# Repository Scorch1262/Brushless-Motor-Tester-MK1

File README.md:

# Brushless-Motor-Tester-MK1

3D-Druck Daten:
https://makerworld.com/de/models/1416815-brushless-motor-tester-mk1

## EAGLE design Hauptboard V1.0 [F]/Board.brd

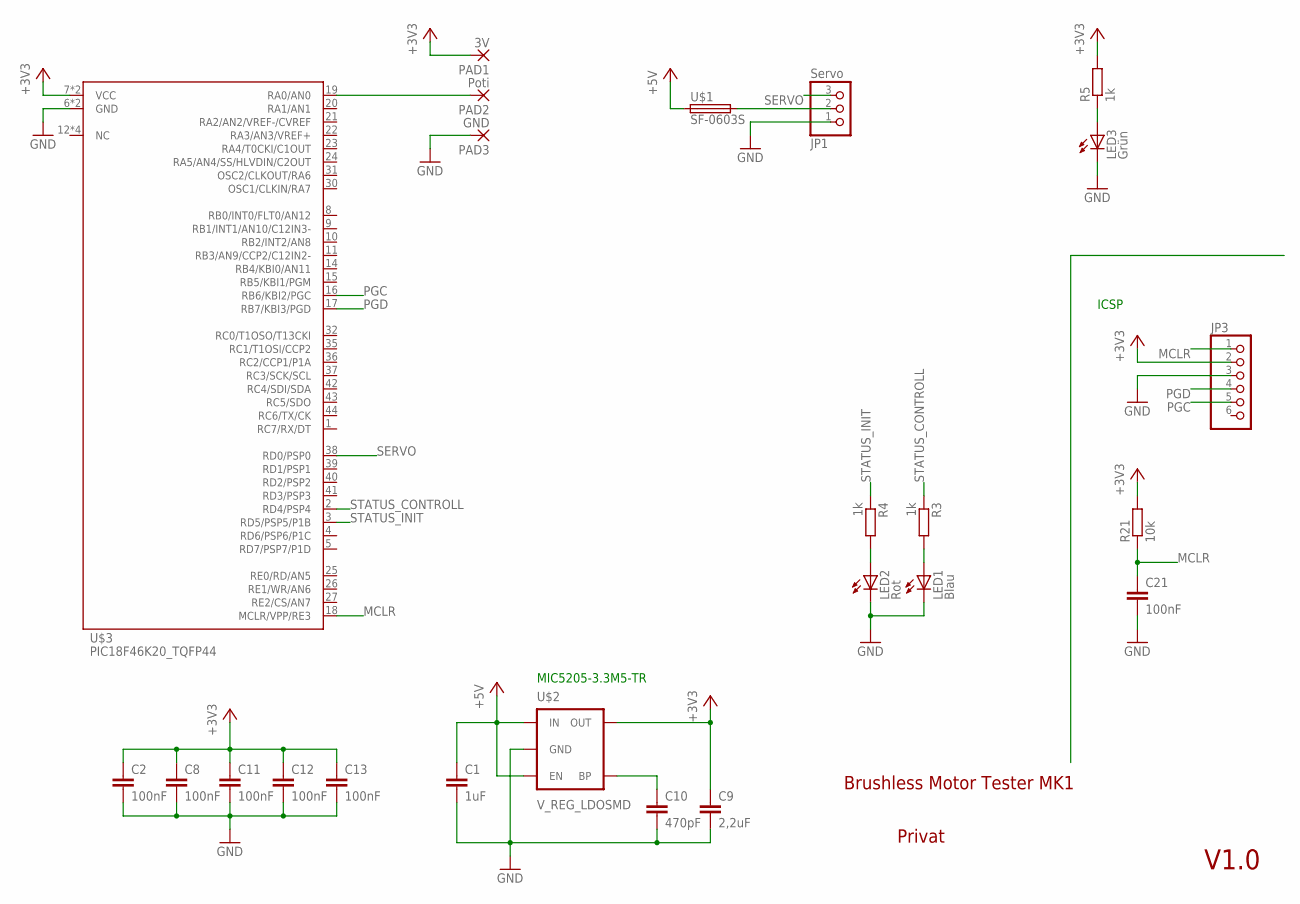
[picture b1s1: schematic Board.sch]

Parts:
C1: 1uF; C0805
C2, C8, C11, C12, C13, C21: 100nF; C0805
C9: 2,2uF; C0805
C10: 470pF; C0805
JP1: Servo; 1X03/90
JP3: PINHD-1X6; 1X06
LED1: Blau; CHIPLED_0805
LED2: Rot; CHIPLED_0805
LED3: Grün; CHIPLED_0805
PAD1: 3V; 5-1,8_50
PAD2: Poti; 5-1,8_50
PAD3: GND; 5-1,8_50
R3, R4, R5: 1k; R0805
R21: 10k; R0805
U$1: SF-0603S; R0603
U$2: V_REG_LDOSMD; SOT23-5
U$3: PIC18F46K20_TQFP44; TQFP44

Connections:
+3V3: C2.1, C8.1, C9.1, C11.1, C12.1, C13.1, JP3.2, PAD1.1, R5.2, R21.2, U$2.5 (OUT), U$3.7 (VCC), U$3.28 (VCC)
+5V: C1.1, U$1.1, U$2.1 (IN), U$2.3 (EN)
GND: C1.2, C2.2, C8.2, C9.2, C10.2, C11.2, C12.2, C13.2, C21.2, JP1.1, JP3.3, LED1.C, LED2.C, LED3.C, PAD3.1, U$2.2 (GND), U$3.6 (GND), U$3.29 (GND)
MCLR: C21.1, JP3.1, R21.1, U$3.18 (MCLR/VPP/RE3)
unnamed: PAD2.1, U$3.19 (RA0/AN0)
unnamed: JP1.2, U$1.2
unnamed: LED3.A, R5.1
unnamed: LED1.A, R3.2
unnamed: LED2.A, R4.2
unnamed: C10.1, U$2.4 (BP)
PGC: JP3.5, U$3.16 (RB6/KBI2/PGC)
PGD: JP3.4, U$3.17 (RB7/KBI3/PGD)
SERVO: JP1.3, U$3.38 (RD0/PSP0)
STATUS_CONTROLL: R3.1, U$3.2 (RD4/PSP4)
STATUS_INIT: R4.1, U$3.3 (RD5/PSP5/P1B)

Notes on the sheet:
Brushless Motor Tester MK1
Privat
V1.0
ICSP
MIC5205-3.3M5-TR

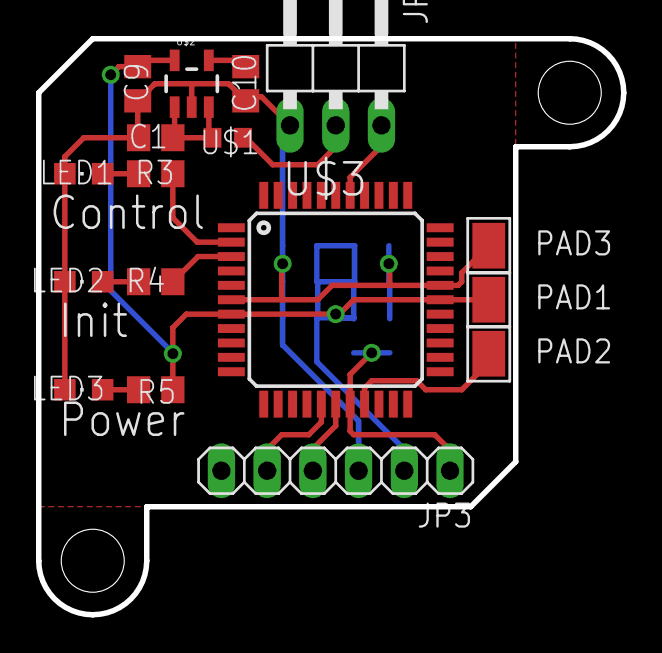
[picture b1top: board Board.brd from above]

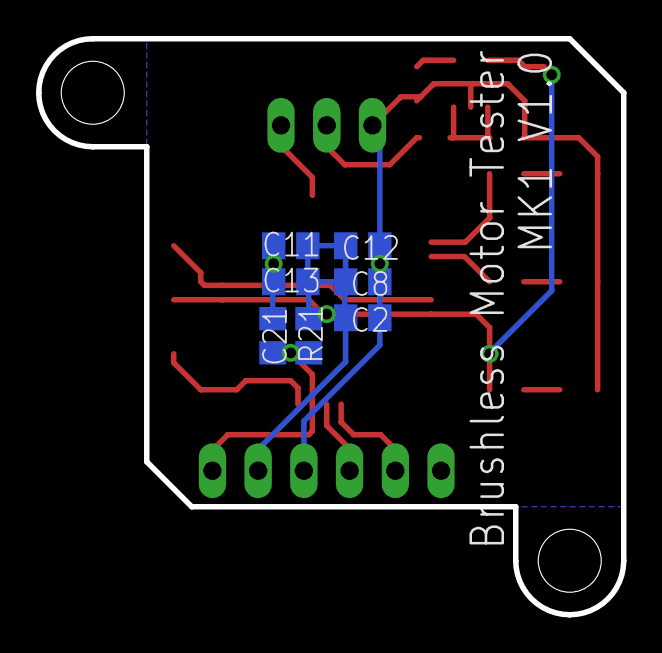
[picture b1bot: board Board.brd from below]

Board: 2 copper layers, 32.5 x 32.0 mm, 24 parts (7 on the bottom side), 15 nets.

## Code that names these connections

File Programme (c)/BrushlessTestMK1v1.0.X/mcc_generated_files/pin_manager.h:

/**
  @Generated Pin Manager Header File

  @Company:
    Microchip Technology Inc.

  @File Name:
    pin_manager.h

  @Summary:
    This is the Pin Manager file generated using PIC10 / PIC12 / PIC16 / PIC18 MCUs

  @Description
    This header file provides APIs for driver for .
    Generation Information :
        Product Revision  :  PIC10 / PIC12 / PIC16 / PIC18 MCUs - 1.81.7
        Device            :  PIC18F46K20
        Driver Version    :  2.11
    The generated drivers are tested against the following:
        Compiler          :  XC8 2.31 and above
        MPLAB 	          :  MPLAB X 5.45	
*/

/*
    (c) 2018 Microchip Technology Inc. and its subsidiaries. 
    
    Subject to your compliance with these terms, you may use Microchip software and any 
    derivatives exclusively with Microchip products. It is your responsibility to comply with third party 
    license terms applicable to your use of third party software (including open source software) that 
    may accompany Microchip software.
    
    THIS SOFTWARE IS SUPPLIED BY MICROCHIP "AS IS". NO WARRANTIES, WHETHER 
    EXPRESS, IMPLIED OR STATUTORY, APPLY TO THIS SOFTWARE, INCLUDING ANY 
    IMPLIED WARRANTIES OF NON-INFRINGEMENT, MERCHANTABILITY, AND FITNESS 
    FOR A PARTICULAR PURPOSE.
    
    IN NO EVENT WILL MICROCHIP BE LIABLE FOR ANY INDIRECT, SPECIAL, PUNITIVE, 
    INCIDENTAL OR CONSEQUENTIAL LOSS, DAMAGE, COST OR EXPENSE OF ANY KIND 
    WHATSOEVER RELATED TO THE SOFTWARE, HOWEVER CAUSED, EVEN IF MICROCHIP 
    HAS BEEN ADVISED OF THE POSSIBILITY OR THE DAMAGES ARE FORESEEABLE. TO 
    THE FULLEST EXTENT ALLOWED BY LAW, MICROCHIP'S TOTAL LIABILITY ON ALL 
    CLAIMS IN ANY WAY RELATED TO THIS SOFTWARE WILL NOT EXCEED THE AMOUNT 
    OF FEES, IF ANY, THAT YOU HAVE PAID DIRECTLY TO MICROCHIP FOR THIS 
    SOFTWARE.
*/

#ifndef PIN_MANAGER_H
#define PIN_MANAGER_H

/**
  Section: Included Files
*/

#include <xc.h>

#define INPUT   1
#define OUTPUT  0

#define HIGH    1
#define LOW     0

#define ANALOG      1
#define DIGITAL     0

#define PULL_UP_ENABLED      1
#define PULL_UP_DISABLED     0

// get/set ADC aliases
#define ADC_TRIS                 TRISAbits.TRISA0
#define ADC_LAT                  LATAbits.LATA0
#define ADC_PORT                 PORTAbits.RA0
#define ADC_ANS                  ANSELbits.ANS0
#define ADC_SetHigh()            do { LATAbits.LATA0 = 1; } while(0)
#define ADC_SetLow()             do { LATAbits.LATA0 = 0; } while(0)
#define ADC_Toggle()             do { LATAbits.LATA0 = ~LATAbits.LATA0; } while(0)
#define ADC_GetValue()           PORTAbits.RA0
#define ADC_SetDigitalInput()    do { TRISAbits.TRISA0 = 1; } while(0)
#define ADC_SetDigitalOutput()   do { TRISAbits.TRISA0 = 0; } while(0)
#define ADC_SetAnalogMode()      do { ANSELbits.ANS0 = 1; } while(0)
#define ADC_SetDigitalMode()     do { ANSELbits.ANS0 = 0; } while(0)

// get/set Servo aliases
#define Servo_TRIS                 TRISDbits.TRISD0
#define Servo_LAT                  LATDbits.LATD0
#define Servo_PORT                 PORTDbits.RD0
#define Servo_SetHigh()            do { LATDbits.LATD0 = 1; } while(0)
#define Servo_SetLow()             do { LATDbits.LATD0 = 0; } while(0)
#define Servo_Toggle()             do { LATDbits.LATD0 = ~LATDbits.LATD0; } while(0)
#define Servo_GetValue()           PORTDbits.RD0
#define Servo_SetDigitalInput()    do { TRISDbits.TRISD0 = 1; } while(0)
#define Servo_SetDigitalOutput()   do { TRISDbits.TRISD0 = 0; } while(0)

// get/set Status_Controll aliases
#define Status_Controll_TRIS                 TRISDbits.TRISD4
#define Status_Controll_LAT                  LATDbits.LATD4
#define Status_Controll_PORT                 PORTDbits.RD4
#define Status_Controll_SetHigh()            do { LATDbits.LATD4 = 1; } while(0)
#define Status_Controll_SetLow()             do { LATDbits.LATD4 = 0; } while(0)
#define Status_Controll_Toggle()             do { LATDbits.LATD4 = ~LATDbits.LATD4; } while(0)
#define Status_Controll_GetValue()           PORTDbits.RD4
#define Status_Controll_SetDigitalInput()    do { TRISDbits.TRISD4 = 1; } while(0)
#define Status_Controll_SetDigitalOutput()   do { TRISDbits.TRISD4 = 0; } while(0)

// get/set Status_Init aliases
#define Status_Init_TRIS                 TRISDbits.TRISD5
#define Status_Init_LAT                  LATDbits.LATD5
#define Status_Init_PORT                 PORTDbits.RD5
#define Status_Init_SetHigh()            do { LATDbits.LATD5 = 1; } while(0)
#define Status_Init_SetLow()             do { LATDbits.LATD5 = 0; } while(0)
#define Status_Init_Toggle()             do { LATDbits.LATD5 = ~LATDbits.LATD5; } while(0)
#define Status_Init_GetValue()           PORTDbits.RD5
#define Status_Init_SetDigitalInput()    do { TRISDbits.TRISD5 = 1; } while(0)
#define Status_Init_SetDigitalOutput()   do { TRISDbits.TRISD5 = 0; } while(0)

/**
   @Param
    none
   @Returns
    none
   @Description
    GPIO and peripheral I/O initialization
   @Example
    PIN_MANAGER_Initialize();
 */
void PIN_MANAGER_Initialize (void);

/**
 * @Param
    none
 * @Returns
    none
 * @Description
    Interrupt on Change Handling routine
 * @Example
    PIN_MANAGER_IOC();
 */
void PIN_MANAGER_IOC(void);



#endif // PIN_MANAGER_H
/**
 End of File
*/

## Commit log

2025-05-14 upload
